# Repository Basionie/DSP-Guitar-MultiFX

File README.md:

# DSP-Guitar-MultiFX

A modular, high-performance guitar multi-effects processor built on the Teensy 4.1. This project features a professional-grade audio graph, real-time parameter control, and a scalable architecture for adding new audio effects.

🛠️ Features
Modular Architecture: Isolated namespaces for DSP, audio routing, and UI logic.

Audio Effects: Currently supports Chorus, Delay, and Reverb.

Hardware Interface: Integrated support for SGTL5000 audio shield, rotary encoder for navigation, and display integration.

Scalable Design: Easily add new effects by implementing the IEffect interface.

🚀 Getting Started
Clone the repository: git clone [https://github.com/Basionie/DSP-Guitar-MultiFX.git](https://github.com/Basionie/DSP-Guitar-MultiFX.git)

Setup: Open the firmware/ folder in VS Code with the PlatformIO extension.

Build: Use the PlatformIO "Build" button to compile the firmware.

Upload: Connect your Teensy 4.1 via USB and click "Upload".

⚙️ How to Add New Effects
To add a new effect (e.g., Distortion):

Create effects/distortion.h and distortion.cpp.

Implement the IEffect interface.

Register the new effect in the EffectManager to enable UI control.

📜 Dependencies
U8g2 (Display driver)

CriticalTaskScheduler 
(Task scheduling)

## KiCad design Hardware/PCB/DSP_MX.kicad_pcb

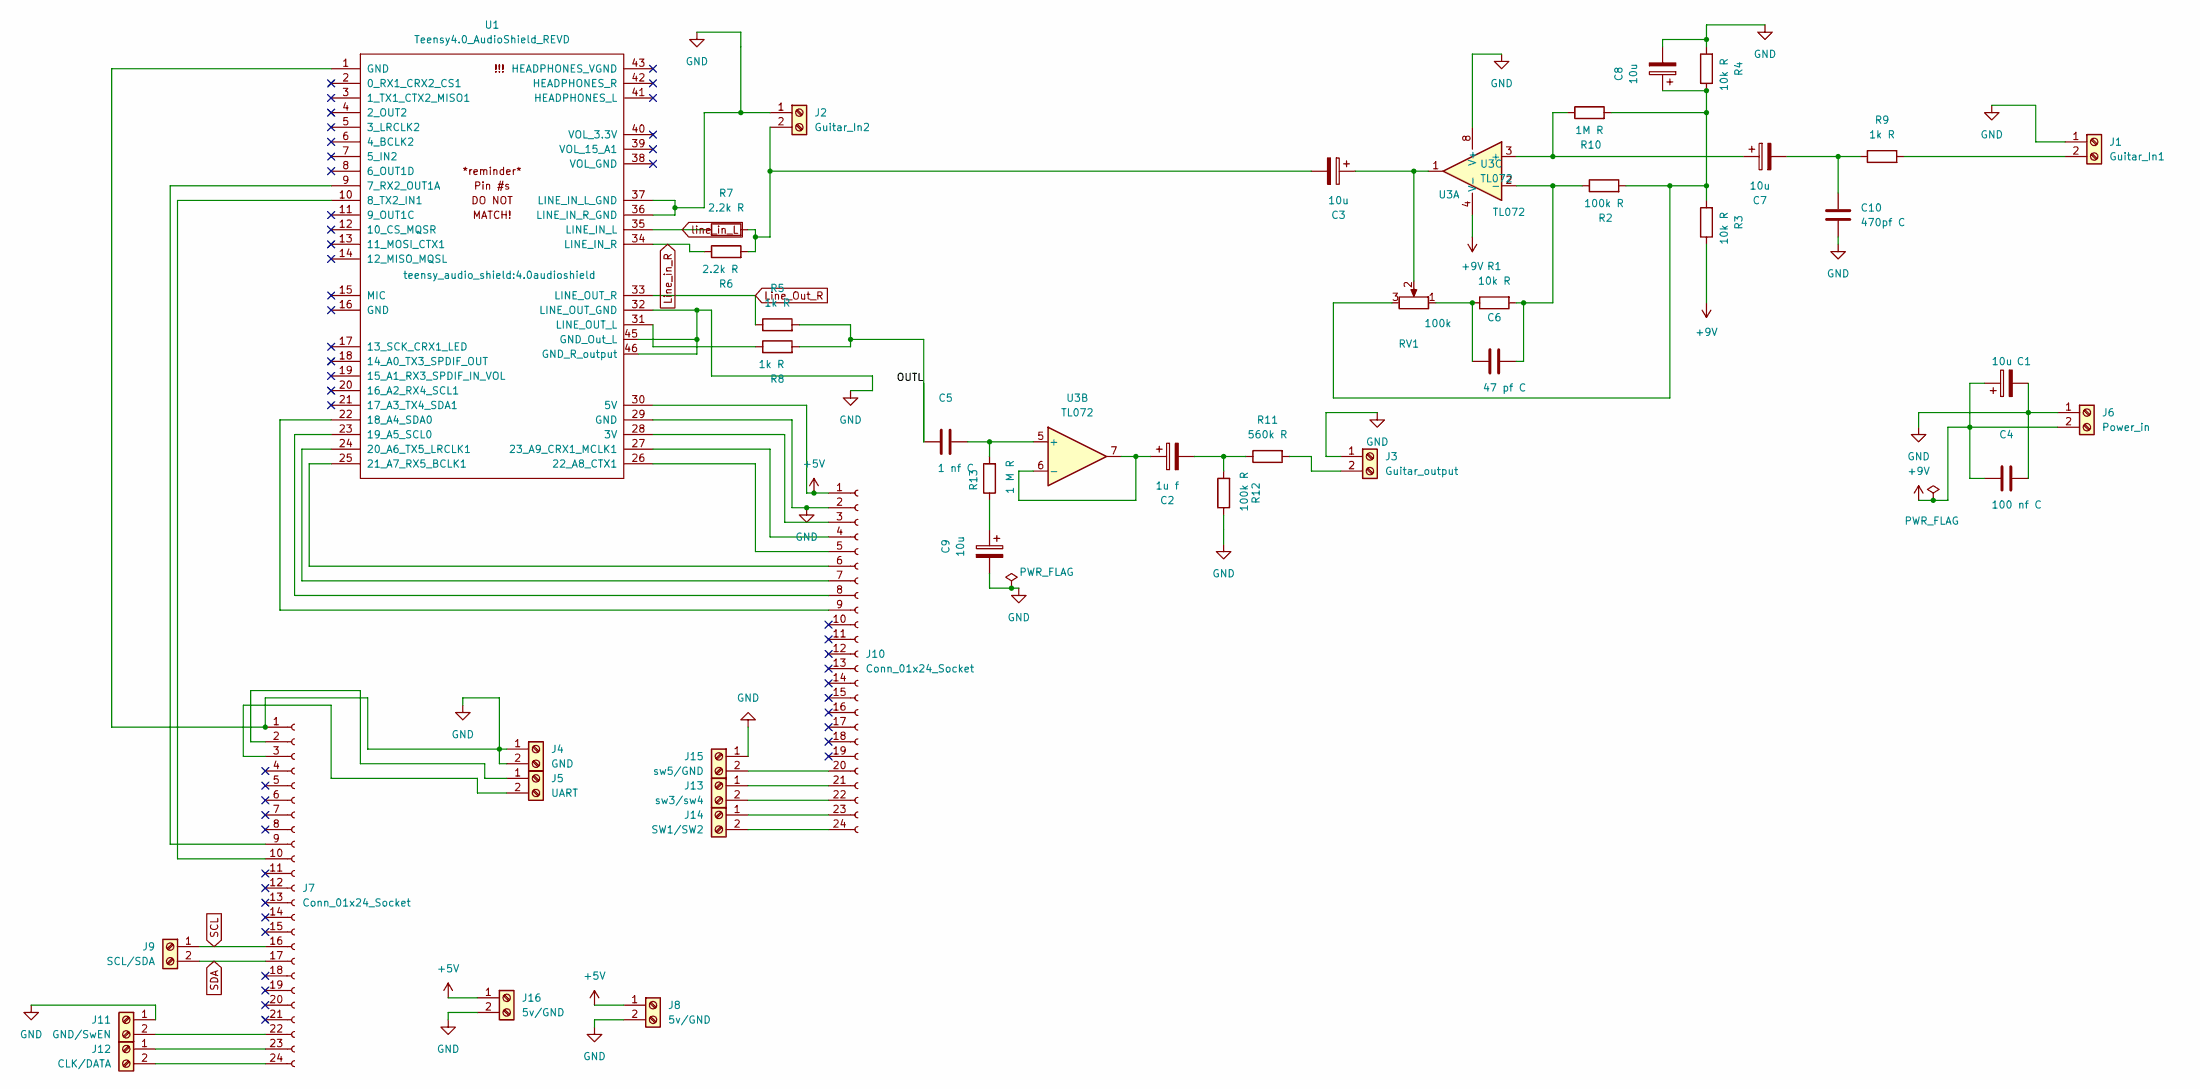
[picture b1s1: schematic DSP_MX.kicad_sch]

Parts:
C1, C3, C7, C8, C9: 10u; CP_Radial_D5.0mm_P2.50mm
C2: 1u f; CP_Radial_D5.0mm_P2.50mm
C4: 100 nf C; C_Radial_D5.0mm_H5.0mm_P2.00mm
C5: 1 nf C; C_Radial_D5.0mm_H5.0mm_P2.00mm
C6: 47 pf C; C_Radial_D5.0mm_H5.0mm_P2.00mm
C10: 470pf C; C_Radial_D5.0mm_H5.0mm_P2.00mm
J1: Guitar_In1; TerminalBlock_Wuerth_691311400102_P7.62mm
J2: Guitar_In2; TerminalBlock_Wuerth_691311400102_P7.62mm
J3: Guitar_output; TerminalBlock_Wuerth_691311400102_P7.62mm
J4: GND; TerminalBlock_Wuerth_691311400102_P7.62mm
J5: UART; TerminalBlock_Wuerth_691311400102_P7.62mm
J6: Power_in; TerminalBlock_Wuerth_691311400102_P7.62mm
J7, J10: Conn_01x24_Socket; PinHeader_1x24_P2.54mm_Vertical
J8, J16: 5v/GND; TerminalBlock_Wuerth_691311400102_P7.62mm
J9: SCL/SDA; TerminalBlock_Wuerth_691311400102_P7.62mm
J11: GND/SwEN; TerminalBlock_Wuerth_691311400102_P7.62mm
J12: CLK/DATA; TerminalBlock_Wuerth_691311400102_P7.62mm
J13: sw3/sw4; TerminalBlock_Wuerth_691311400102_P7.62mm
J14: SW1/SW2; TerminalBlock_Wuerth_691311400102_P7.62mm
J15: sw5/GND; TerminalBlock_Wuerth_691311400102_P7.62mm
R1, R3, R4: 10k R; R_Axial_DIN0207_L6.3mm_D2.5mm_P7.62mm_Horizontal
R2, R12: 100k R; R_Axial_DIN0207_L6.3mm_D2.5mm_P7.62mm_Horizontal
R5, R8, R9: 1k R; R_Axial_DIN0207_L6.3mm_D2.5mm_P7.62mm_Horizontal
R6, R7: 2.2k R; R_Axial_DIN0207_L6.3mm_D2.5mm_P7.62mm_Horizontal
R10: 1M R; R_Axial_DIN0207_L6.3mm_D2.5mm_P7.62mm_Horizontal
R11: 560k R; R_Axial_DIN0207_L6.3mm_D2.5mm_P7.62mm_Horizontal
R13: 1 M R; R_Axial_DIN0207_L6.3mm_D2.5mm_P7.62mm_Horizontal
RV1: 100k; Potentiometer_Runtron_RM-065_Vertical
U1: Teensy4.0_AudioShield_REVD; 4.0audioshield
U3: TL072; CERDIP-8_W7.62mm_SideBrazed_Socket

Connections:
+5V: J8.1, J10.1, J16.1, U1.30 (5V)
+9V: C1.1, C4.2, J6.2, R3.1, U3.4 (V-)
/OUTL: C5.2, R5.2, R8.2
GND: C1.2, C4.1, C8.2, C9.2, C10.2, J1.1, J2.1, J3.1, J4.1, J4.2, J6.1, J7.1, J8.2, J10.2, J11.1, J15.1, J16.2, R4.2, R12.1, U1.1 (GND), U1.29 (GND), U1.32 (LINE_OUT_GND), U1.36 (LINE_IN_R_GND), U1.37 (LINE_IN_L_GND), U1.45 (GND_Out_L), U1.46 (GND_R_output), U3.8 (V+)
Line_Out_R: R5.1, U1.33 (LINE_OUT_R)
Line_in_R: R6.1, U1.34 (LINE_IN_R)
unnamed: C2.2, R11.1, R12.2
unnamed: C3.1, RV1.2, U3.1
unnamed: C6.2, R1.1, RV1.1
unnamed: C8.1, R2.2, R3.2, R4.1, R10.2, RV1.3
unnamed: C9.1, R13.1
unnamed: C7.2, C10.1, R9.1
unnamed: J1.2, R9.2
unnamed: C3.2, J2.2, R6.2, R7.2
unnamed: J3.2, R11.2
unnamed: J5.1, J7.2
unnamed: J5.2, J7.3
unnamed: J7.9, U1.9 (7_RX2_OUT1A)
unnamed: J7.10, U1.10 (8_TX2_IN1)
unnamed: J10.3, U1.28 (3V)
unnamed: J10.4, U1.27 (23_A9_CRX1_MCLK1)
unnamed: J10.5, U1.26 (22_A8_CTX1)
unnamed: J10.6, U1.25 (21_A7_RX5_BCLK1)
unnamed: J10.7, U1.24 (20_A6_TX5_LRCLK1)
unnamed: J10.8, U1.23 (19_A5_SCL0)
unnamed: J10.9, U1.22 (18_A4_SDA0)
unnamed: J10.20, J15.2
unnamed: J10.21, J13.1
unnamed: J10.22, J13.2
unnamed: J10.23, J14.1
unnamed: J10.24, J14.2
unnamed: J7.22, J11.2
unnamed: J7.23, J12.1
unnamed: J7.24, J12.2
unnamed: R8.1, U1.31 (LINE_OUT_L)
unnamed: C7.1, R10.1, U3.3 (+)
unnamed: C6.1, R1.2, R2.1, U3.2 (-)
unnamed: C5.1, R13.2, U3.5 (+)
unnamed: C2.1, U3.6 (-), U3.7
SCL: J7.16, J9.1
SDA: J7.17, J9.2
line_in_L: R7.1, U1.35 (LINE_IN_L)

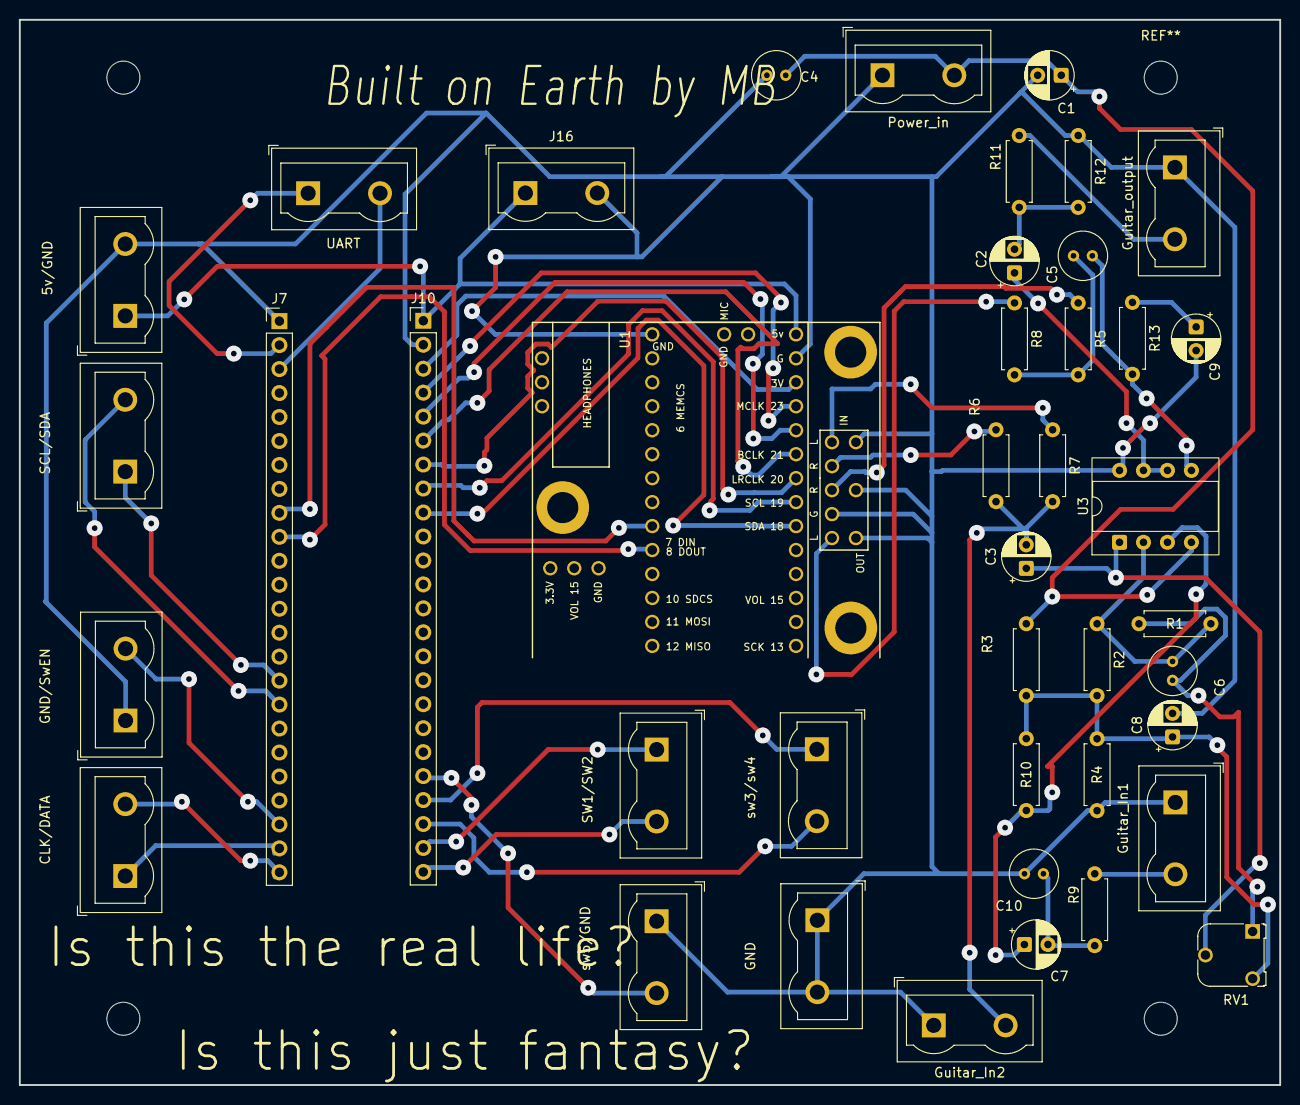
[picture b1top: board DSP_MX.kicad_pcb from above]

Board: 2 copper layers, 133.6 x 112.9 mm, 42 parts (0 on the bottom side), 42 nets.

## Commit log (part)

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2026-06-18 Initial DSP Guitar Teensy project
